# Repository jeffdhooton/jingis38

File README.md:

# Jingis 38 Keyboard

This is an ergonomic, 38-key, VIAL compatible keyboard based off of the corne/crkbd but with a larger column stagger. I designed the board to be hotswap, and use cheap SMD components, and a 3D printed case.

## BOM

You will need all of the following to build one of these boards.

1. PCBs from a PCB manufacturer (JLCPCB cost me $18 for 5 of these boards)

2. Pro Micro ATMega32U4

3. 1N1418 SMD Diodes

4. Kailh Hotswap Sockets

5. MX Keyswitches

6. MX Keycaps

7. M2 Heatset Inserts

8. M2x10 standoff screws

9. CA Glue

## Build Process

Once you receive your PCBs in, and have all of your components - you're ready to build. Building this board should be pretty straight forward for anybody that's done so for other boards before. If you haven't, then the build process is as follows:

**Solder SMD components**

The first step is to tin one side of the pads for every diode spot on the board. Once you have tinned the pads, you're ready to solder the components on. Make sure that you're soldering diodes on with the correct polarity. Diodes should have a line on one side of them, so make sure this lines up with the point of the triangle on the PCB. If you solder them on backwards, you're going to have a bad time.

Kailh hotswap sockets should come second. My process for soldering these is similar to the diodes - tin one of the pads for every spot on the board, solder the component to the tinned pad and then when done with the whole board, come back and add solder to the other pad, completing the connection

**Solder Pro Micro**

The next step is to solder on the MCU headers. The MCU on this board goes on top of the board. Place the header pins through the top of the board and solder on the back. Tack one pin on for each side and then ensure that the headers are vertical in their slots and not leaning to one side or the other.

After you've got the headers attached to the board you can solder the MCU to the headers. The MCU for this board should be upside down, with the USB-C port facing the board instead of facing away from the board.

**Prepare Case for Install**

The case prints in 4 pieces. Two halves and then two switch plates. There are also butterfly mechanisms on the build plate for connecting the two halves of the case. Align the two halves of the case, put some super glue in the butterfly slots on the case and then put the joiners in those slots.

When the glue sets, install heatset inserts into every standoff hole in the case. These should be M2 standoffs so that you can get screws through the holes on the PCB.

**Install Switches & Assemble Board**

Place the switches into the plates that you've printed off, and then line the plates up against the board and press down. Make sure you don't bend any switch pins during this process.

When you have switches on each side attached to the board via the hotswap sockets place the completed PCB into the case. Use M2x10 standoff screws through the holes on the switch plates to attach the board to the case. When you've got them all added the board should feel secure.

**Flash Firmware**

Check out [the readme](/jingis/readme.md) in the `jingis` directory of this repository for instructions on how to flash the firmware.

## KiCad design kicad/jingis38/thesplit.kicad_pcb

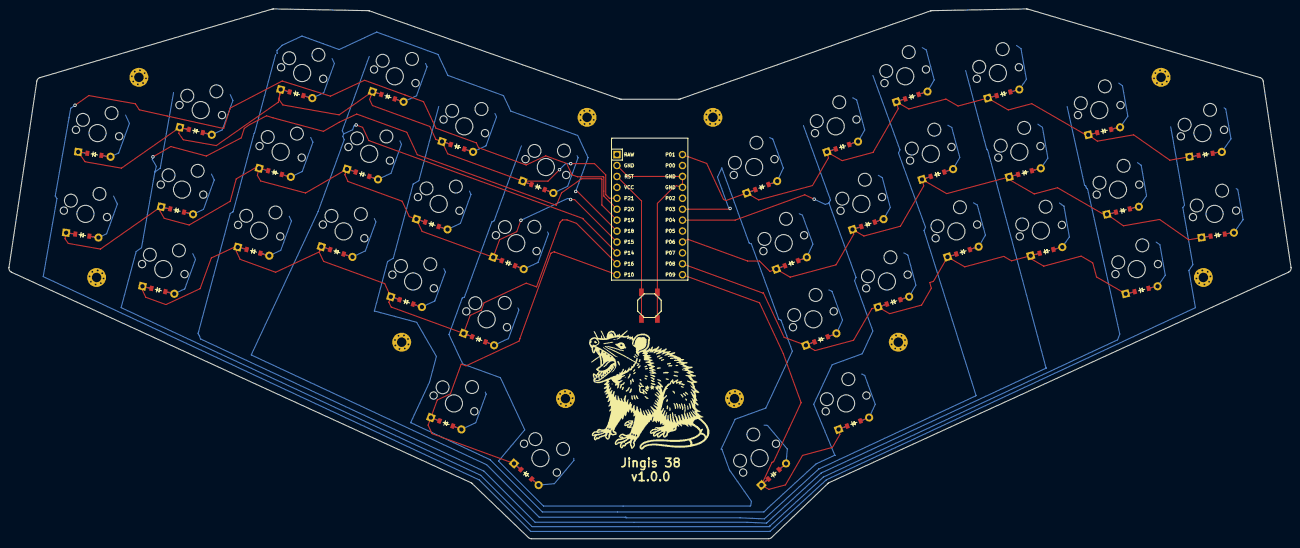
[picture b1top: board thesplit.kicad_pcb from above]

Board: 2 copper layers, 298.3 x 123.3 mm, 88 parts (0 on the bottom side), 54 nets.

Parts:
B1: SW_TACT_ALPS_SKQGABE010
D1, D2, D3, D4, D5, D6, D7, D8, D9, D10, D11, D12, D13, D14, D15, D16, D17, D18, D19, D20, D21, D22, D23, D24, D25, D26, D27, D28, D29, D30, D31, D32, D33, D34, D35, D36, D37, D38: ComboDiode
MCU1: ProMicro
S1, S2, S3, S4, S5, S6, S7, S8, S9, S10, S11, S12, S13, S14, S15, S16, S17, S18, S19, S20, S21, S22, S23, S24, S25, S26, S27, S28, S29, S30, S31, S32, S33, S34, S35, S36, S37, S38: MX
_1, _2, _3, _4, _5, _6, _7, _8, _9, _10: MountingHole_2.2mm_M2_Pad_Via

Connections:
GND: B1.1, MCU1.2, MCU1.15, MCU1.16
P1: D21.1, D24.1, D27.1, D30.1, D33.1, D36.1, MCU1.13
P3: MCU1.18, S15.1, S16.1, S17.1, S19.1, S34.1, S35.1, S36.1, S38.1
P4: MCU1.19, S12.1, S13.1, S14.1, S18.1, S31.1, S32.1, S33.1, S37.1
P6: D20.1, D23.1, D26.1, D29.1, D32.1, D35.1, MCU1.21
P8: D22.1, D25.1, D28.1, D31.1, D34.1, MCU1.23
P9: D37.1, D38.1, MCU1.24
P10: D18.1, D19.1, MCU1.12
P14: MCU1.10, S9.1, S10.1, S11.1, S28.1, S29.1, S30.1
P15: D1.1, D4.1, D7.1, D10.1, D13.1, D16.1, MCU1.9
P16: D3.1, D6.1, D9.1, D12.1, D15.1, MCU1.11
P18: MCU1.8, S6.1, S7.1, S8.1, S25.1, S26.1, S27.1
P19: MCU1.7, S3.1, S4.1, S5.1, S22.1, S23.1, S24.1
P20: MCU1.6, S1.1, S2.1, S20.1, S21.1
P21: D2.1, D5.1, D8.1, D11.1, D14.1, D17.1, MCU1.5
RST: B1.2, MCU1.3
home_thumb: D19.2, S19.2
index_bottom: D12.2, S12.2
index_home: D13.2, S13.2
index_top: D14.2, S14.2
inner_bottom: D15.2, S15.2
inner_home: D16.2, S16.2
inner_top: D17.2, S17.2
middle_bottom: D9.2, S9.2
middle_home: D10.2, S10.2
middle_top: D11.2, S11.2
mirror_home_thumb: D38.2, S38.2
mirror_index_bottom: D31.2, S31.2
mirror_index_home: D32.2, S32.2
mirror_index_top: D33.2, S33.2
mirror_inner_bottom: D34.2, S34.2
mirror_inner_home: D35.2, S35.2
mirror_inner_top: D36.2, S36.2
mirror_middle_bottom: D28.2, S28.2
mirror_middle_home: D29.2, S29.2
mirror_middle_top: D30.2, S30.2
mirror_near_thumb: D37.2, S37.2
mirror_outer_home: D20.2, S20.2
mirror_outer_top: D21.2, S21.2
mirror_pinky_bottom: D22.2, S22.2
mirror_pinky_home: D23.2, S23.2
mirror_pinky_top: D24.2, S24.2
mirror_ring_bottom: D25.2, S25.2
mirror_ring_home: D26.2, S26.2
mirror_ring_top: D27.2, S27.2
near_thumb: D18.2, S18.2
outer_home: D1.2, S1.2
outer_top: D2.2, S2.2
pinky_bottom: D3.2, S3.2
pinky_home: D4.2, S4.2
pinky_top: D5.2, S5.2
ring_bottom: D6.2, S6.2
ring_home: D7.2, S7.2
ring_top: D8.2, S8.2

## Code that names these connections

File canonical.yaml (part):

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    autobind: 10
    skip: false
    asym: both
    colrow: pinky_bottom
    name: matrix_pinky_bottom
    zone: *ref_1
    col: *ref_2
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    autobind: 10
    skip: false
    asym: both
    colrow: pinky_home
    name: matrix_pinky_home
    zone: *ref_1
    col: *ref_2
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    autobind: 10
    skip: false
    asym: both
    colrow: pinky_top
    name: matrix_pinky_top
    zone: *ref_1
    col: *ref_2
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    autobind: 10
    skip: false
    asym: both
    colrow: mirror_pinky_bottom
    name: mirror_matrix_pinky_bottom
    zone:
      columns:
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    autobind: 10
    skip: false
    asym: both
    colrow: mirror_pinky_home
    name: mirror_matrix_pinky_home
    zone:
      columns:
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    autobind: 10
    skip: false
    asym: both
    colrow: mirror_pinky_top
    name: mirror_matrix_pinky_top
    zone:
      columns:
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
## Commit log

2024-07-01 keypos
2024-07-01 outline
2024-07-01 pre-net-running
2024-07-01 local ergogen
2024-07-02 V1 - off to the printers
2024-07-02 remove node modules & package.json
2024-07-12 jingis
2024-07-13 getting closer
2024-07-13 it compiles
2024-07-13 still trying to work out the layout/matrix
2024-07-14 holding
2024-07-14 so close
2024-07-14 flashes
2024-07-14 flashes 2
2024-07-14 row 2 working
2024-07-14 it flashes, full map
2024-07-14 working on vial support
2024-07-14 reduce firmware size
2024-07-14 home row mods
2024-07-25 readme info
